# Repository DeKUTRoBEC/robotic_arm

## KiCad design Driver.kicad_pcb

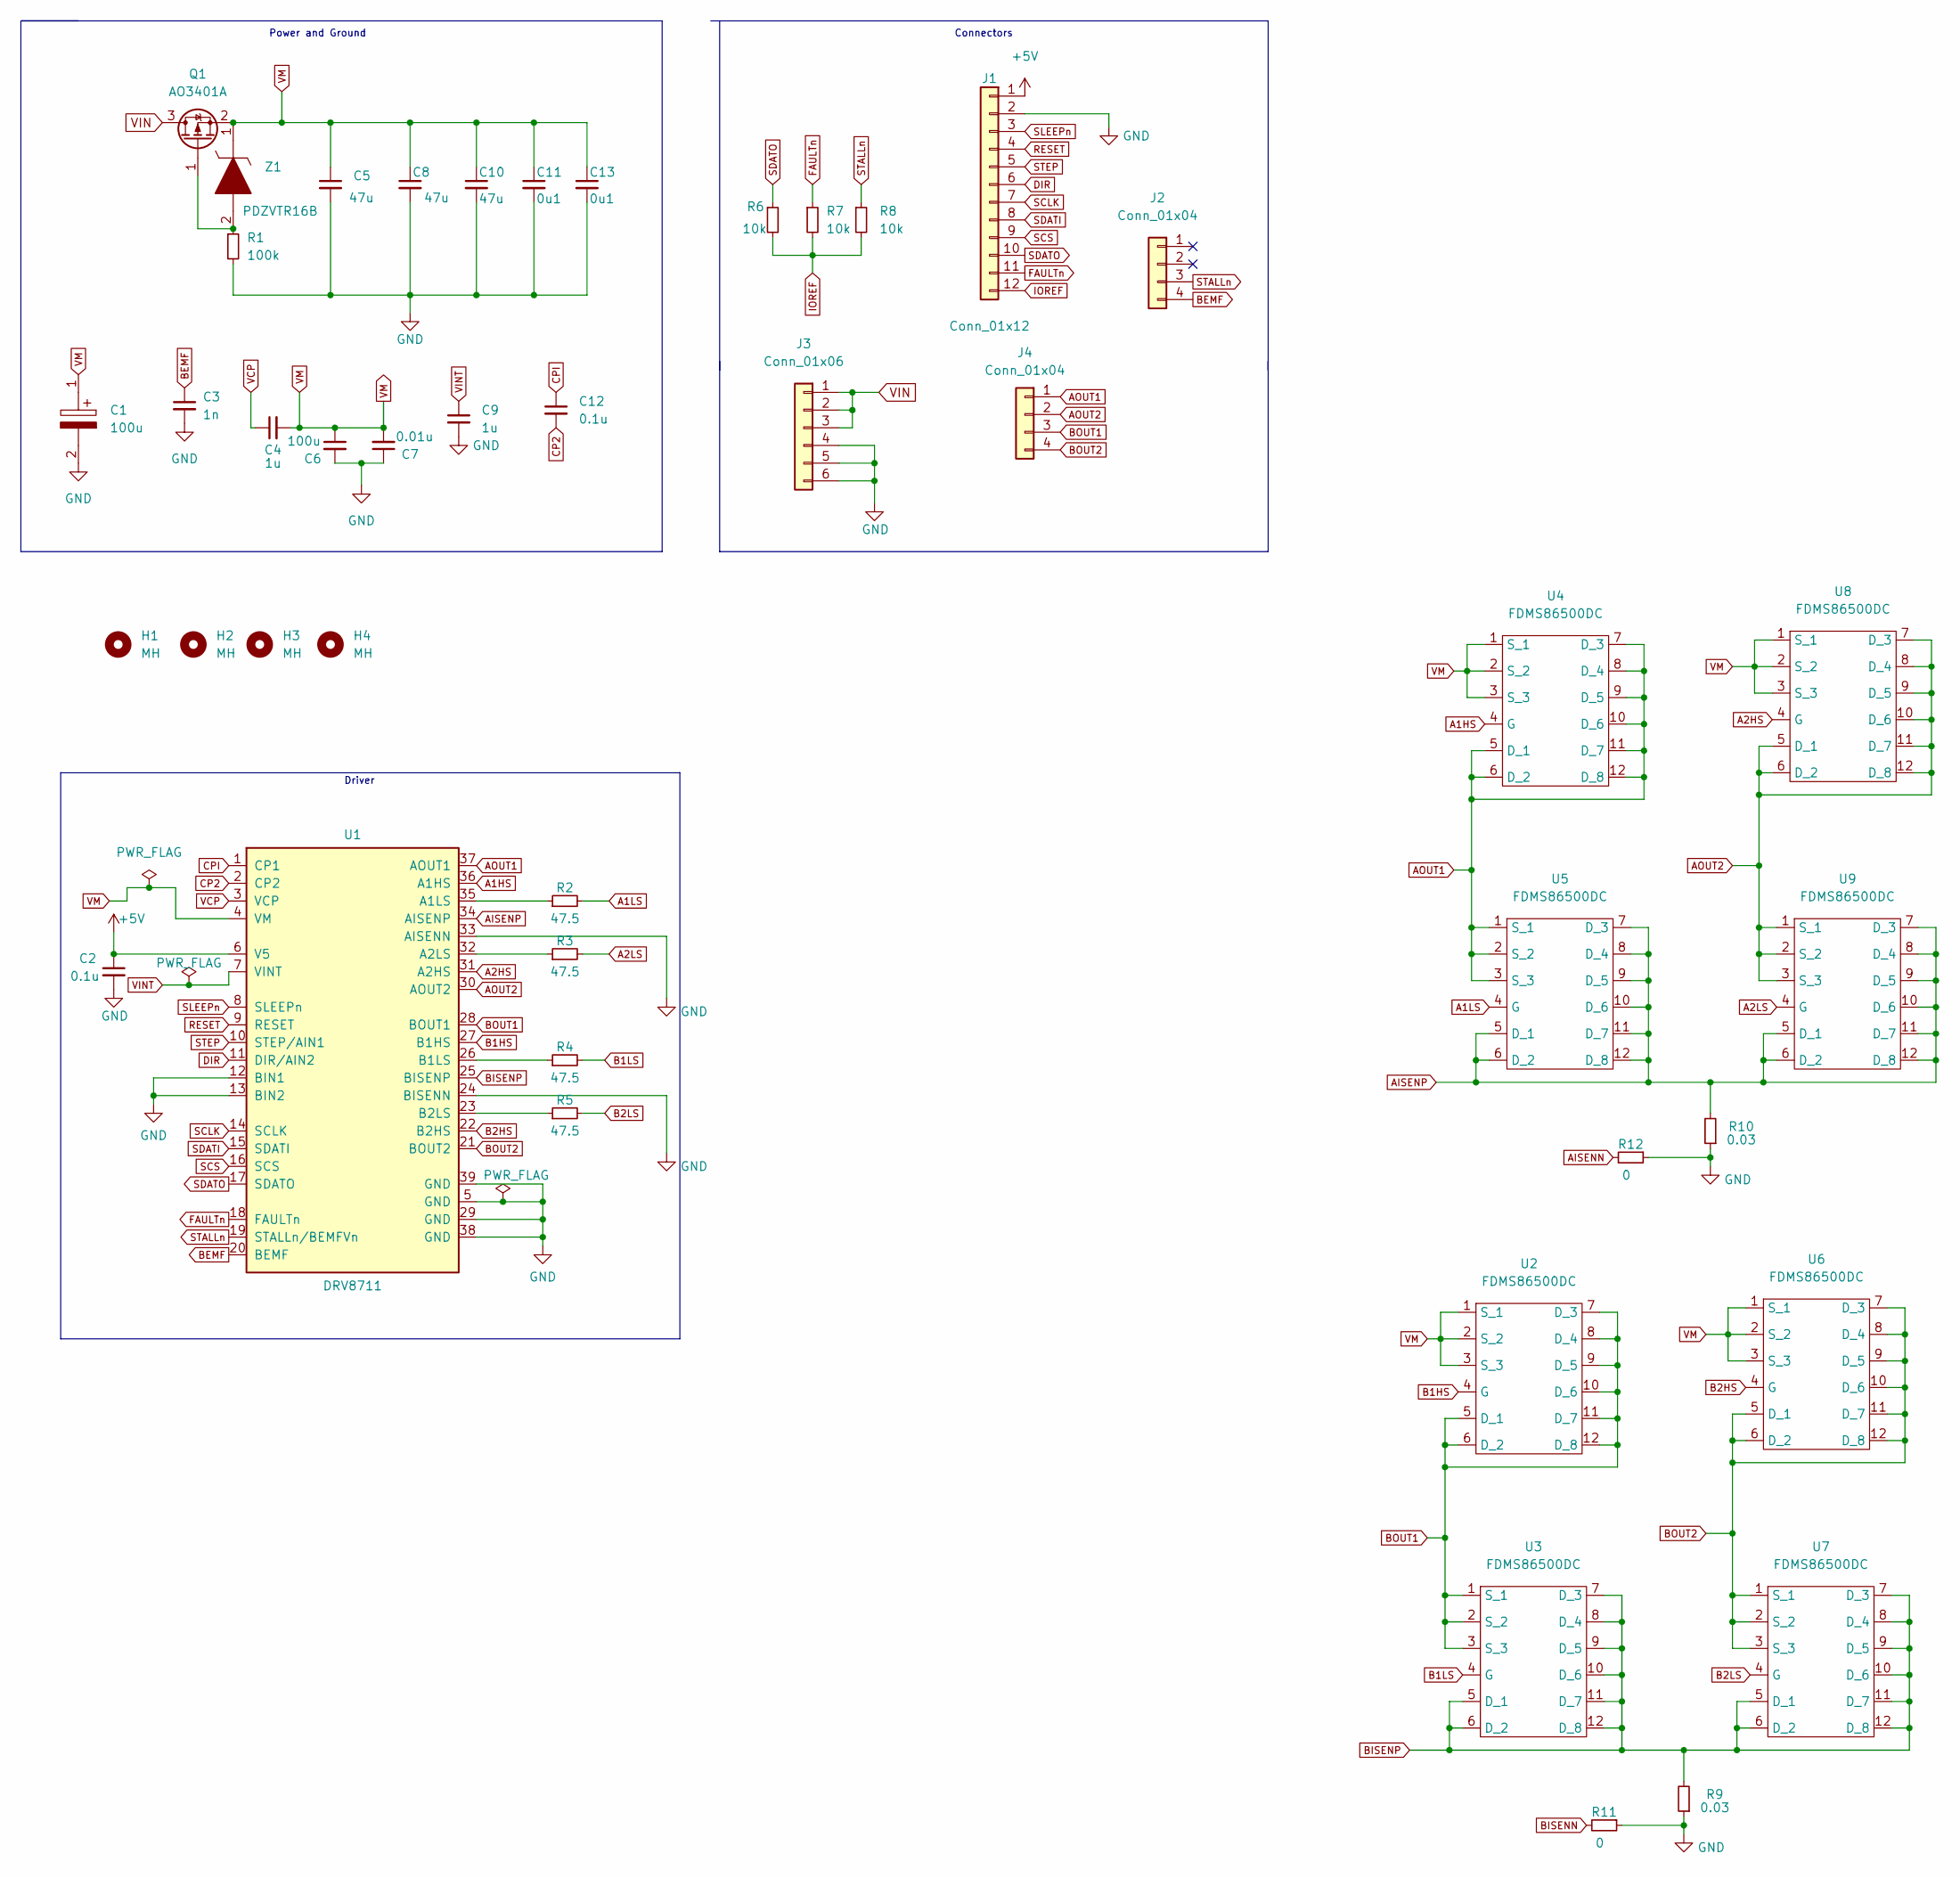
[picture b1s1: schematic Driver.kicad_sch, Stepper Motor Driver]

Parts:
C1: 100u; CAPPRD500W60D1025H1400; Manufacturer_Part_Number 35ZLH100MEFC6.3X11; Mouser Part Number 232-35ZLH100MEFC63X1
C2, C12: 0.1u; C_0603_1608Metric
C3: 1n; C_0603_1608Metric
C4, C9: 1u; C_0402_1005Metric
C5, C8, C10: 47u; C_0402_1005Metric
C6: 100u; C_0402_1005Metric
C7: 0.01u; C_0603_1608Metric
C11, C13: 0u1; C_0603_1608Metric
H1, H2, H3, H4: MH; MountingHole_2.2mm_M2_Pad_Via
J1: Conn_01x12; PinHeader_1x12_P1.00mm_Vertical
J2, J4: Conn_01x04; PinHeader_1x04_P1.00mm_Vertical
J3: Conn_01x06; PinHeader_1x06_P1.00mm_Vertical
Q1: AO3401A; SOT-23
R1: 100k; R_0603_1608Metric
R2, R3, R4, R5: 47.5; R_0201_0603Metric
R6, R7, R8: 10k; R_0603_1608Metric
R9, R10: 0.03; RESC2012X65N
R11, R12: 0; RESC2012X65N
U1: DRV8711; SOP50P640X120-39N
U2, U3, U4, U5, U6, U7, U8, U9: FDMS86500DC; FDMS86500L
Z1: PDZVTR16B; Manufacturer_Part_Number PDZVTR16B; Mouser Part Number 755-PDZVTR16B

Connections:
+5V: C2.1, J1.1, U1.6 (V5)
A1HS: U1.36 (A1HS), U4.4 (G)
A1LS: R2.2, U5.4 (G)
A2HS: U1.31 (A2HS), U8.4 (G)
A2LS: R3.2, U9.4 (G)
AISENN: R12.2
AOUT1: J4.1, U1.37 (AOUT1), U4.5 (D_1), U4.6 (D_2), U4.7 (D_3), U4.8 (D_4), U4.9 (D_5), U4.10 (D_6), U4.11 (D_7), U4.12 (D_8), U5.1 (S_1), U5.2 (S_2), U5.3 (S_3)
AOUT2: J4.2, U1.30 (AOUT2), U8.5 (D_1), U8.6 (D_2), U8.7 (D_3), U8.8 (D_4), U8.9 (D_5), U8.10 (D_6), U8.11 (D_7), U8.12 (D_8), U9.1 (S_1), U9.2 (S_2), U9.3 (S_3)
B1HS: U1.27 (B1HS), U2.4 (G)
B1LS: R4.2, U3.4 (G)
B2HS: U1.22 (B2HS), U6.4 (G)
B2LS: R5.2, U7.4 (G)
BEMF: C3.1, J2.4, U1.20 (BEMF)
BISENN: R11.2
BOUT1: J4.3, U1.28 (BOUT1), U2.5 (D_1), U2.6 (D_2), U2.7 (D_3), U2.8 (D_4), U2.9 (D_5), U2.10 (D_6), U2.11 (D_7), U2.12 (D_8), U3.1 (S_1), U3.2 (S_2), U3.3 (S_3)
BOUT2: J4.4, U1.21 (BOUT2), U6.5 (D_1), U6.6 (D_2), U6.7 (D_3), U6.8 (D_4), U6.9 (D_5), U6.10 (D_6), U6.11 (D_7), U6.12 (D_8), U7.1 (S_1), U7.2 (S_2), U7.3 (S_3)
CP2: C12.2, U1.2 (CP2)
CPI: C12.1, U1.1 (CP1)
DIR: J1.6, U1.11 (DIR/AIN2)
FAULTn: J1.11, R7.1, U1.18 (FAULTn)
GND: C1.2, C2.2, C3.2, C5.2, C6.2, C7.1, C8.2, C9.2, C10.2, C11.2, C13.2, J1.2, J3.4, J3.5, J3.6, R1.2, R9.1, R10.1, R11.1, R12.1, U1.5 (GND), U1.12 (BIN1), U1.13 (BIN2), U1.24 (BISENN), U1.29 (GND), U1.33 (AISENN), U1.38 (GND), U1.39 (GND); also elsewhere on the board
IOREF: J1.12, R6.2, R7.2, R8.2
unnamed: Q1.1 (G), R1.1, Z1.2
unnamed: R2.1, U1.35 (A1LS)
unnamed: R3.1, U1.32 (A2LS)
unnamed: R4.1, U1.26 (B1LS)
unnamed: R5.1, U1.23 (B2LS)
RESET: J1.4, U1.9 (RESET)
SCLK: J1.7, U1.14 (SCLK)
SCS: J1.9, U1.16 (SCS)
SDATI: J1.8, U1.15 (SDATI)
SDATO: J1.10, R6.1, U1.17 (SDATO)
SLEEPn: J1.3, U1.8 (SLEEPn)
STALLn: J2.3, R8.1, U1.19 (STALLn/BEMFVn)
STEP: J1.5, U1.10 (STEP/AIN1)
VCP: C4.1, U1.3 (VCP)
VIN: J3.1, J3.2, J3.3, Q1.3 (D)
VINT: C9.1, U1.7 (VINT)
VM: C1.1, C4.2, C5.1, C6.1, C7.2, C8.1, C10.1, C11.1, C13.1, Q1.2 (S), U1.4 (VM), U2.1 (S_1), U2.2 (S_2), U2.3 (S_3), U4.1 (S_1), U4.2 (S_2), U4.3 (S_3), U6.1 (S_1), U6.2 (S_2), U6.3 (S_3), U8.1 (S_1), U8.2 (S_2), U8.3 (S_3), Z1.1

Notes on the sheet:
Power and Ground
Connectors
Driver

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
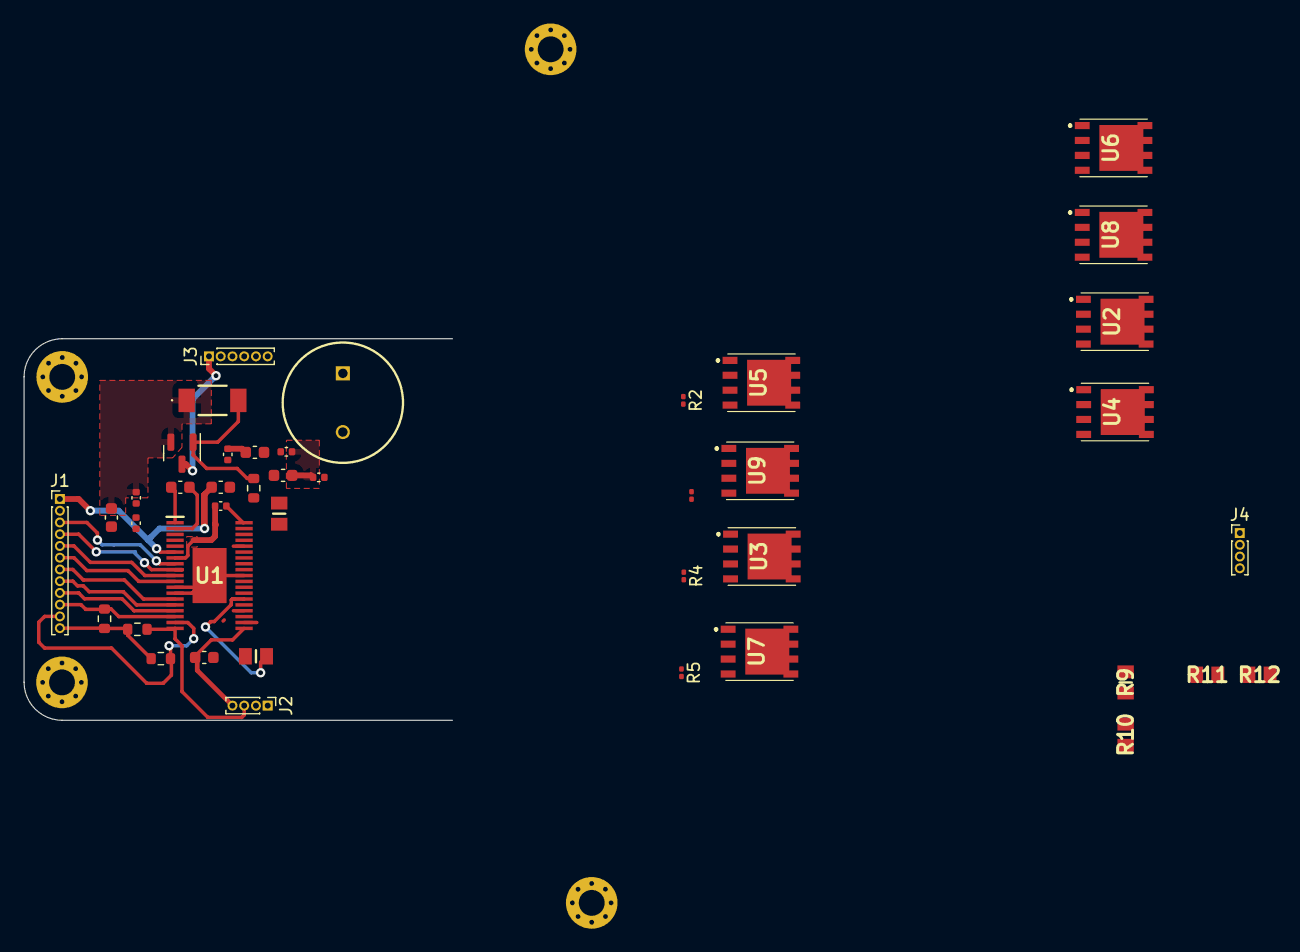
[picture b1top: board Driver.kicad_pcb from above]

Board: 2 copper layers, 46 parts (0 on the bottom side), 39 nets.

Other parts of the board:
R9#2, R10#2: 0.03; RESC2012X65N

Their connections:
GND: R9#2.1, R10#2.1; also elsewhere on the board

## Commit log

2022-11-23 Driver files added
